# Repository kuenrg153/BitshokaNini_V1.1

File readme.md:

```
Open Source is Intrinsic to Bitcoin
```
# The Bitshoka Nini V1.1
The Bitshoka Nini V1.1 is based off of the Bitaxe Gamma EXCEPT it uses the KF1950 ASIC from MicroBT / Whatsminer.
Huge shoutout to skot for all the work he did create this ecosystem!
The primary aim Bitshoka Nini is to bring microBT ASICs to the Bitaxe ecosystem. A secondary goal is to make a low cost and readily available Bitaxe variant in Africa.
We hope that this is the first of a number of contributions the Bitshoka team can make to the bitcoin network.
Shoka is "axe" and Nini is "what" in Swahili.

# The bitaxe
bitaxe is a fully open source Bitcoin ASIC miner aimed at decentralizing mining. 

## Goals
- **Easy**: Just plug it in and mine Bitcoin over WiFi. No external computer needed.
- **Practical**: low cost, low noise, low power, low maintenance. You can run this at home.
- **ASIC Power**: High efficiency and hashrate, based on the latest and greatest Application Specific Integrated Circuits.
- **Versatile**: Mine to any StratumV1 pool, Lottery mine, Solo mine, Or hack it to do whatever you want.
- **Bitcoin Ethos**: Fully open source, permissionless and decentralized to support the worldwide freedom money.

## ASIC
At the heart of the bitaxeGamma is a BM1370 Bitcoin mining ASIC from the Antminer S21 Pro from Bitmain. It's not open source.

- Bitmain claims the BM1370 has 15 J/TH efficiency. We can get pretty close to that with the BitaxeGamma
- The Antminer S21 Pro has a nominal hashrate of 234 TH/s. There are 3 hashboards with 65 chips each, for a total of 195 chips. The bitaxeGamma has a single one of these chips. That means _about_ 1.2 TH/s per bitaxeGamma. Initial testing looks good!
- The BM1370 is brand new and isn't available individually yet. The best place to get these chips is right out of a S21 Pro.
- The BM1370 has a different footprint and pinout from the BM1368, BM1366, BM1397 and BM1387 in previous bitaxe.

## Current Status
- BitaxeGamma 600 is working well and has been released!
- In addition to higher hashrate, the Gamma also uses more power. Please pay attemtion to hash frequency and voltage settings as it's much easier to overheat, especially when using the stock heatsink and fan.
- BM1370 firmware support has been added to [esp-miner](https://github.com/skot/esp-miner)
- Be sure to check the [HW issues](https://github.com/skot/bitaxe/issues) for known bugs, reworks and errata.
- This is an _advanced_ build! You can do it, but if you're not looking for a project, it might be best to buy one pre-assembled from one of the [many sellers](https://bitaxe.org/legit.html). Check [Skot's method](assembly.md) of hand assembling PCBs.

## PCB Hardware
This repo contains all of the design files for the PCB. [KiCAD](https://www.kicad.com) software is used. There is a BOM file for all of the components that get soldered to the PCB. 

- Order PCBs from your favorite PCB shop, like [JLCPCB](https://jlcpcb.com), [SeeedStudio](https://www.seeedstudio.com/fusion_pcb.html), or [PCBWay](https://www.pcbway.com)
    - Gerbers are in the `Manufacturing Files` dir. PCBs are 4-layer, 6mil trace/space and 0.3mm hole compatible. 1oz outer / 0.5oz inner layer thickness works well.
    - Make sure to order stencils too. These are the "paste" layers in the gerbers folder. one for top and one for bottom.
- All PCB parts except the ASIC are available from [DigiKey](https://www.digikey.com/en/products) and others. You can find Digikey part numbers on the DK tab of the BOM

## Extra Hardware
There are a few other hardware components that are needed for a complete bitaxe.

- **Heatsink**
	- [40x40mm heatsink and 5V fan](https://www.aliexpress.com/item/2251832861666365.html) from a random AliExpress seller. The fans are crap, but the heatsinks are good.  
- **Fan**
	- You **must** have active cooling on the bitaxe. The heatsink alone is not enough.
	- The Bitaxe has a connector for a 4pin, 5V PWM fan. 40mm square, 20mm thick fans work nicely with the suggested heatsink. Make sure to get a 5V fan! 12V spin, but slowly overheating your Bitaxe..
	- Upgrade your fan with the [Noctua NF-A4x10](https://noctua.at/en/nf-a4x10-5v-pwm) 5V 4-Pin fan for a much more pleasant experience.
- **Thermal compound**
	- Use a good quality thermal compound between the heatsink and ASIC. [Thermal Grizzly Kryonaut](https://www.amazon.com/Thermal-Grizzly-Kryonaut-Grease-Paste/dp/B011F7W3LU) has been known to work well.  
- **Display**
	- Supports 0.91" SSD1306-based I2C OLED Module. [Example Amazon seller](https://www.amazon.com/gp/product/B08ZY4YBHL). Make sure to get the male pins to interface with the Bitaxe PCB. 
- **Power Supply**
	- **5V DC Only!** Anything else will damage the Bitaxe. Be careful and double-check your power supply is 5V. Many other voltage power supplies use the same connector.
	- The power supply needs to supply in excess of 4A (20W) and not drop below 5V. Often times you have to use a power supply rated for 25-30W to get this!
 		- The [Meanwell GST60A05-P1J](https://www.digikey.com/en/products/detail/mean-well-usa-inc/GST60A05-P1J/7703709) at 30 Watts is the cadillac of 5V PSUs and is working well with the Gamma.  
	- The bitaxe uses a 5.5x2.1mm, center-positive barrel jack. 5.5x2.5mm plugs have been known to work.
- **Stand**
	- The PCB has corner mounting holes. You're going to want a stand to mount your Bitaxe. Many excellent 3D printed designs are available.

## Firmware
- The [ESP-Miner](https://github.com/skot/ESP-Miner) has initial support for the BM1370 ASIC. Improvements are ongoing.

### ESP32 Programming Requirements
- As of the bitaxeUltra, all ESP32 programming is done through a USB-C cable and connector on the bitaxe. See [ESP-Miner](https://github.com/skot/ESP-Miner) for more details.

## More Information
- Project page at [bitaxe.org](https://bitaxe.org)
- [Open Source Miners United](discord.gg/osmu) Discord chat
- [building.md](building.md) for PCB ordering tips
- [assembly.md](assembly.md) for assembly tips

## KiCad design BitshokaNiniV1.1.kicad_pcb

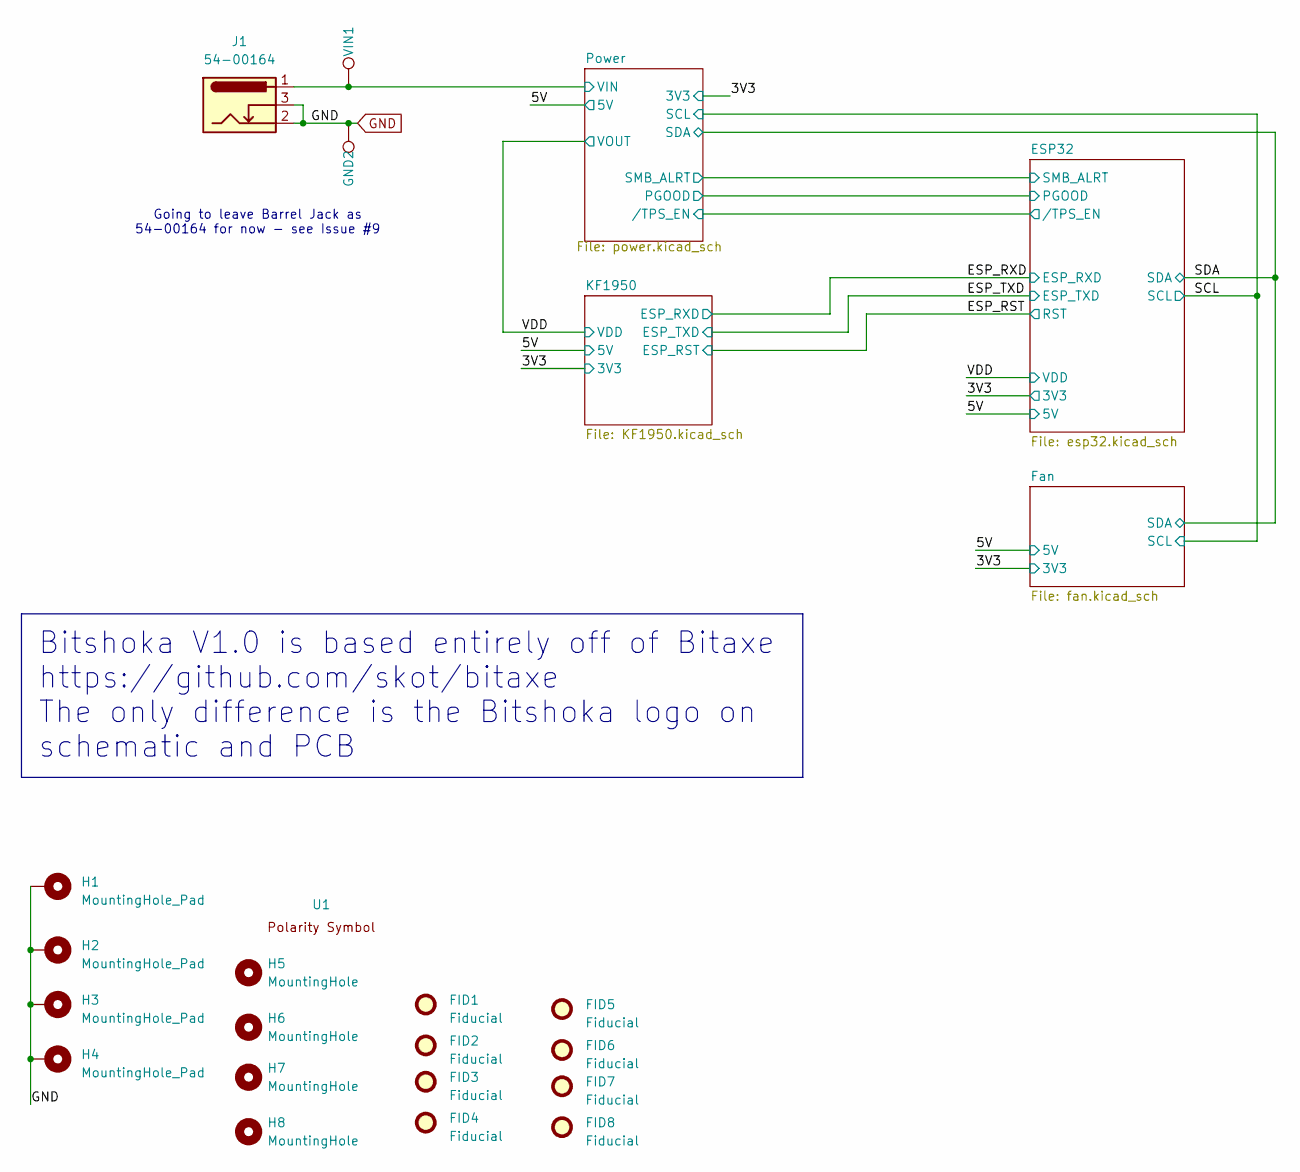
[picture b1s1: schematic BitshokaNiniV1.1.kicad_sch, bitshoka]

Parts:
FID1, FID2, FID3, FID4, FID5, FID6, FID7, FID8: Fiducial; Fiducial_1mm_Mask2mm
GND2: TestPoint; TestPoint_Pad_D1.5mm
H1, H2, H3, H4: MountingHole_Pad; MountingHole_3mm_Pad_Via
H5, H6, H7, H8: MountingHole; MountingHole_3.5mm
J1: 54-00164; TENSILITY_54-00164; PARTNO 54-00164; LCSC C431534
U1: polarity
VIN1: TestPoint; TestPoint_Pad_D1.5mm

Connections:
/5V: J1.1, VIN1.1; also elsewhere on the board
GND: GND2.1, H1.1, H2.1, H3.1, H4.1, J1.2, J1.3; also elsewhere on the board

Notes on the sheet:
Going to leave Barrel Jack as 54-00164 for now - see Issue #9
Bitshoka V1.0 is based entirely off of Bitaxe https://github.com/skot/bitaxe The only difference is the Bitshoka logo on schematic and PCB

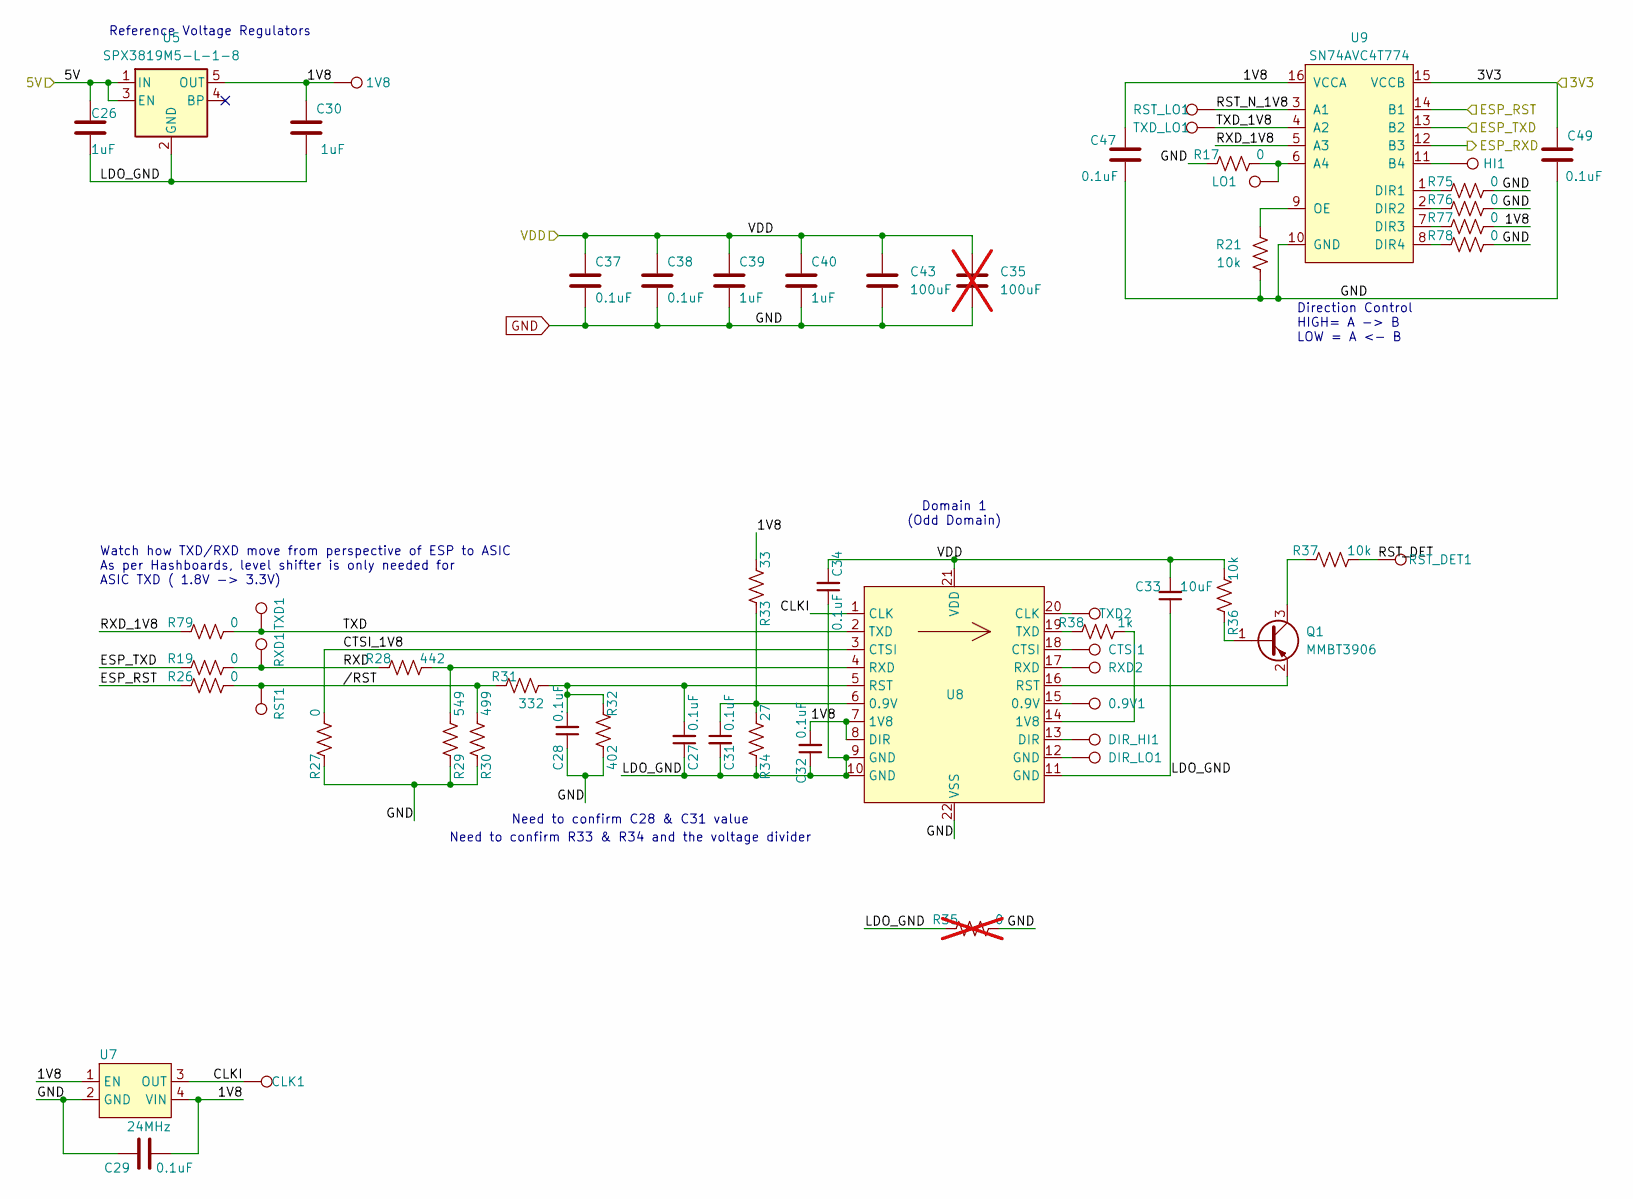
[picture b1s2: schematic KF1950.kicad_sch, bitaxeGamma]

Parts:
0.9V1: TestPoint; TestPoint_Pad_D1.0mm
1V8: TestPoint; TestPoint_Pad_D1.5mm
C26, C30, C39, C40: 1uF; C_0402_1005Metric; PARTNO EMK105BJ105MV-F
C27, C28, C31, C32, C34: 0.1uF; C_0402_1005Metric
C29, C37, C38, C47, C49: 0.1uF; C_0402_1005Metric; PARTNO CL05A104KO5NNNC
C33: 10uF; C_0805_2012Metric
C35: 100uF; C_1206_3216Metric; not fitted
C43: 100uF; C_1206_3216Metric
CLK1: TestPoint; TestPoint_Pad_D1.5mm
CTSI1: TestPoint; TestPoint_Pad_D1.0mm
DIR_HI1: TestPoint; TestPoint_Pad_D1.0mm
DIR_LO1: TestPoint; TestPoint_Pad_D1.0mm
HI1: TestPoint; TestPoint_Pad_D1.5mm
LO1: TestPoint; TestPoint_Pad_D1.5mm
Q1: MMBT3906; SOT-23
R17, R19, R26, R27, R79: 0; R_0402_1005Metric
R21: 10k; R_0402_1005Metric; PARTNO RC0402FR-0720KL
R28: 442; R_0402_1005Metric
R29: 549; R_0402_1005Metric
R30: 499; R_0402_1005Metric
R31: 332; R_0402_1005Metric
R32: 402; R_0402_1005Metric
R33: 33; R_0402_1005Metric
R34: 27; R_0402_1005Metric
R35: 0; R_0402_1005Metric; not fitted
R36, R37: 10k; R_0402_1005Metric
R38: 1k; R_0402_1005Metric
R75, R76, R77, R78: 0; R_0402_1005Metric; PARTNO RC0402FR-0720KL
RST1: TestPoint; TestPoint_Pad_D1.5mm
RST_DET1: TestPoint; TestPoint_Pad_D1.5mm
RST_LO1: TestPoint; TestPoint_Pad_D1.5mm
RXD1: TestPoint; TestPoint_Pad_D1.5mm
RXD2: TestPoint; TestPoint_Pad_D1.0mm
TXD1: TestPoint; TestPoint_Pad_D1.5mm
TXD2: TestPoint; TestPoint_Pad_D1.0mm
TXD_LO1: TestPoint; TestPoint_Pad_D1.5mm
U5: SPX3819M5-L-1-8; SOT-23-5
U7: 24MHz; SMD3225-4P; PARTNO SX3M25.000E20F30THN; LCSC C5137262
U8: KF1950
U9: SN74AVC4T774; TSSOP-16_4.4x5mm_P0.65mm; PARTNO SN74AVC4T774PWR

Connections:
/3V3: C49.1, U9.15 (VCCB); also elsewhere on the board
/5V: C26.1, U5.1 (IN), U5.3 (EN); also elsewhere on the board
/ESP_RST: R26.1, U9.14 (B1); also elsewhere on the board
/ESP_RXD: U9.12 (B3); also elsewhere on the board
/ESP_TXD: R19.1, U9.13 (B2); also elsewhere on the board
/KF1950/1V8: 1V8.1, C29.2, C30.1, C32.2, C47.1, R33.2, R77.1, U5.5 (OUT), U7.1 (EN), U7.4 (VIN), U8.7 (1V8), U8.8 (DIR), U9.16 (VCCA)
/KF1950/CLKI: CLK1.1, U7.3 (OUT), U8.1 (CLK)
/KF1950/CTSI_1V8: R27.2, U8.3 (CTSI)
/KF1950/LDO_GND: C26.2, C27.1, C30.2, C31.2, C32.1, C33.1, C34.1, R34.1, R35.1, U5.2 (GND), U8.9 (GND), U8.10 (GND), U8.11 (GND)
/KF1950/RST_DET: R37.2, RST_DET1.1
/KF1950/RST_N_1V8: RST_LO1.1, U9.3 (A1)
/KF1950/RXD: R19.2, R28.1, RXD1.1
/KF1950/RXD_1V8: R79.1, U9.5 (A3)
/KF1950/TXD: R79.2, TXD1.1, U8.2 (TXD)
/KF1950/TXD_1V8: TXD_LO1.1, U9.4 (A2)
/KF1950//RST: R26.2, R30.2, R31.1, RST1.1
/VDD: C33.2, C34.2, C35.1, C37.1, C38.1, C39.1, C40.1, C43.1, R36.1, U8.21 (VDD); also elsewhere on the board
GND: C28.1, C29.1, C35.2, C37.2, C38.2, C39.2, C40.2, C43.2, C47.2, C49.2, R17.1, R21.1, R27.1, R29.1, R30.1, R32.2, R35.2, R75.1, R76.1, R78.1, U7.2 (GND), U8.22 (VSS), U9.10 (GND); also elsewhere on the board
unnamed: 0.9V1.1, U8.15 (0.9V)
unnamed: C27.2, C28.2, R31.2, R32.1, U8.5 (RST)
unnamed: C31.1, R33.1, R34.2, U8.6 (0.9V)
unnamed: CTSI1.1, U8.18 (CTSI)
unnamed: DIR_HI1.1, U8.13 (DIR)
unnamed: DIR_LO1.1, U8.12 (GND)
unnamed: Q1.1 (B), R36.2
unnamed: Q1.3 (C), R37.1
unnamed: Q1.2 (E), U8.16 (RST)
unnamed: R28.2, R29.2, U8.4 (RXD)
unnamed: R38.1, U8.14 (1V8)
unnamed: R38.2, U8.19 (TXD)
unnamed: RXD2.1, U8.17 (RXD)
unnamed: TXD2.1, U8.20 (CLK)
unnamed: LO1.1, R17.2, U9.6 (A4)
unnamed: HI1.1, U9.11 (B4)
unnamed: R75.2, U9.1 (DIR1)
unnamed: R76.2, U9.2 (DIR2)
unnamed: R77.2, U9.7 (DIR3)
unnamed: R78.2, U9.8 (DIR4)
unnamed: R21.2, U9.9 (OE)

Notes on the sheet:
Reference Voltage Regulators
Need to confirm C28 & C31 value
Domain 1 (Odd Domain)
Direction Control HIGH= A -> B LOW = A <- B
Watch how TXD/RXD move from perspective of ESP to ASIC As per Hashboards, level shifter is only needed for ASIC TXD ( 1.8V -> 3.3V)
Need to confirm R33 & R34 and the voltage divider

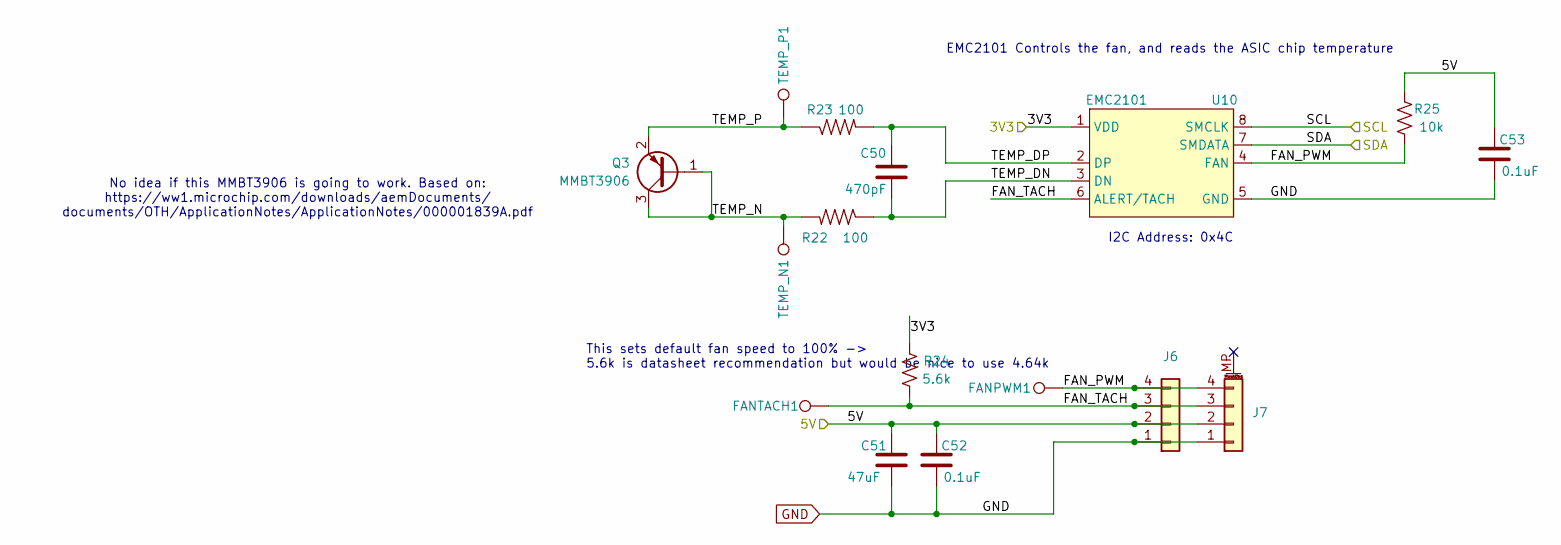
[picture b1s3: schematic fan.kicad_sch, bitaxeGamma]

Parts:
C50: 470pF; C_0402_1005Metric; PARTNO CL05B471KB5NNNC
C51: 47uF; C_1210_3225Metric; PARTNO CL32A476KOJNNNE
C52, C53: 0.1uF; C_0402_1005Metric; PARTNO CL05A104KO5NNNC
FANPWM1: TestPoint; TestPoint_Pad_D1.5mm
FANTACH1: TestPoint; TestPoint_Pad_D1.5mm
J6: Conn_01x04; 470531000; PARTNO 0470531000
J7: Conn_01x04; JST_SH_BM04B-SRSS-TB_1x04-1MP_P1.00mm_Vertical
Q3: MMBT3906; SOT-23
R22, R23: 100; R_0402_1005Metric; PARTNO RC0402FR-07100RL
R24: 5.6k; R_0402_1005Metric; PARTNO RC0402FR-135K6L
R25: 10k; R_0402_1005Metric; PARTNO RC0402JR-0710KL
TEMP_N1: TestPoint; TestPoint_Pad_D1.5mm
TEMP_P1: TestPoint; TestPoint_Pad_D1.5mm
U10: EMC2101; TSSOP-8_3x3mm_P0.65mm; PARTNO EMC2101-R-ACZL-TR

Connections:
/3V3: R24.2, U10.1 (VDD); also elsewhere on the board
/5V: C51.1, C52.1, C53.1, J6.2, J7.2, R25.2; also elsewhere on the board
/Fan/FAN_PWM: FANPWM1.1, J6.4, J7.4, R25.1, U10.4 (FAN)
/Fan/FAN_TACH: FANTACH1.1, J6.3, J7.3, R24.1, U10.6 (ALERT/TACH)
/Fan/TEMP_DN: C50.2, R22.1, U10.3 (DN)
/Fan/TEMP_DP: C50.1, R23.2, U10.2 (DP)
/Fan/TEMP_N: Q3.1 (B), Q3.3 (C), R22.2, TEMP_N1.1
/Fan/TEMP_P: Q3.2 (E), R23.1, TEMP_P1.1
/SCL: U10.8 (SMCLK); also elsewhere on the board
/SDA: U10.7 (SMDATA); also elsewhere on the board
GND: C51.2, C52.2, C53.2, J6.1, J7.1, U10.5 (GND); also elsewhere on the board

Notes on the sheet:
EMC2101 Controls the fan, and reads the ASIC chip temperature
This sets default fan speed to 100% -> 5.6k is datasheet recommendation but would be nice to use 4.64k
No idea if this MMBT3906 is going to work. Based on: https://ww1.microchip.com/downloads/aemDocuments/ documents/OTH/ApplicationNotes/ApplicationNotes/000001839A.pdf
I2C Address: 0x4C

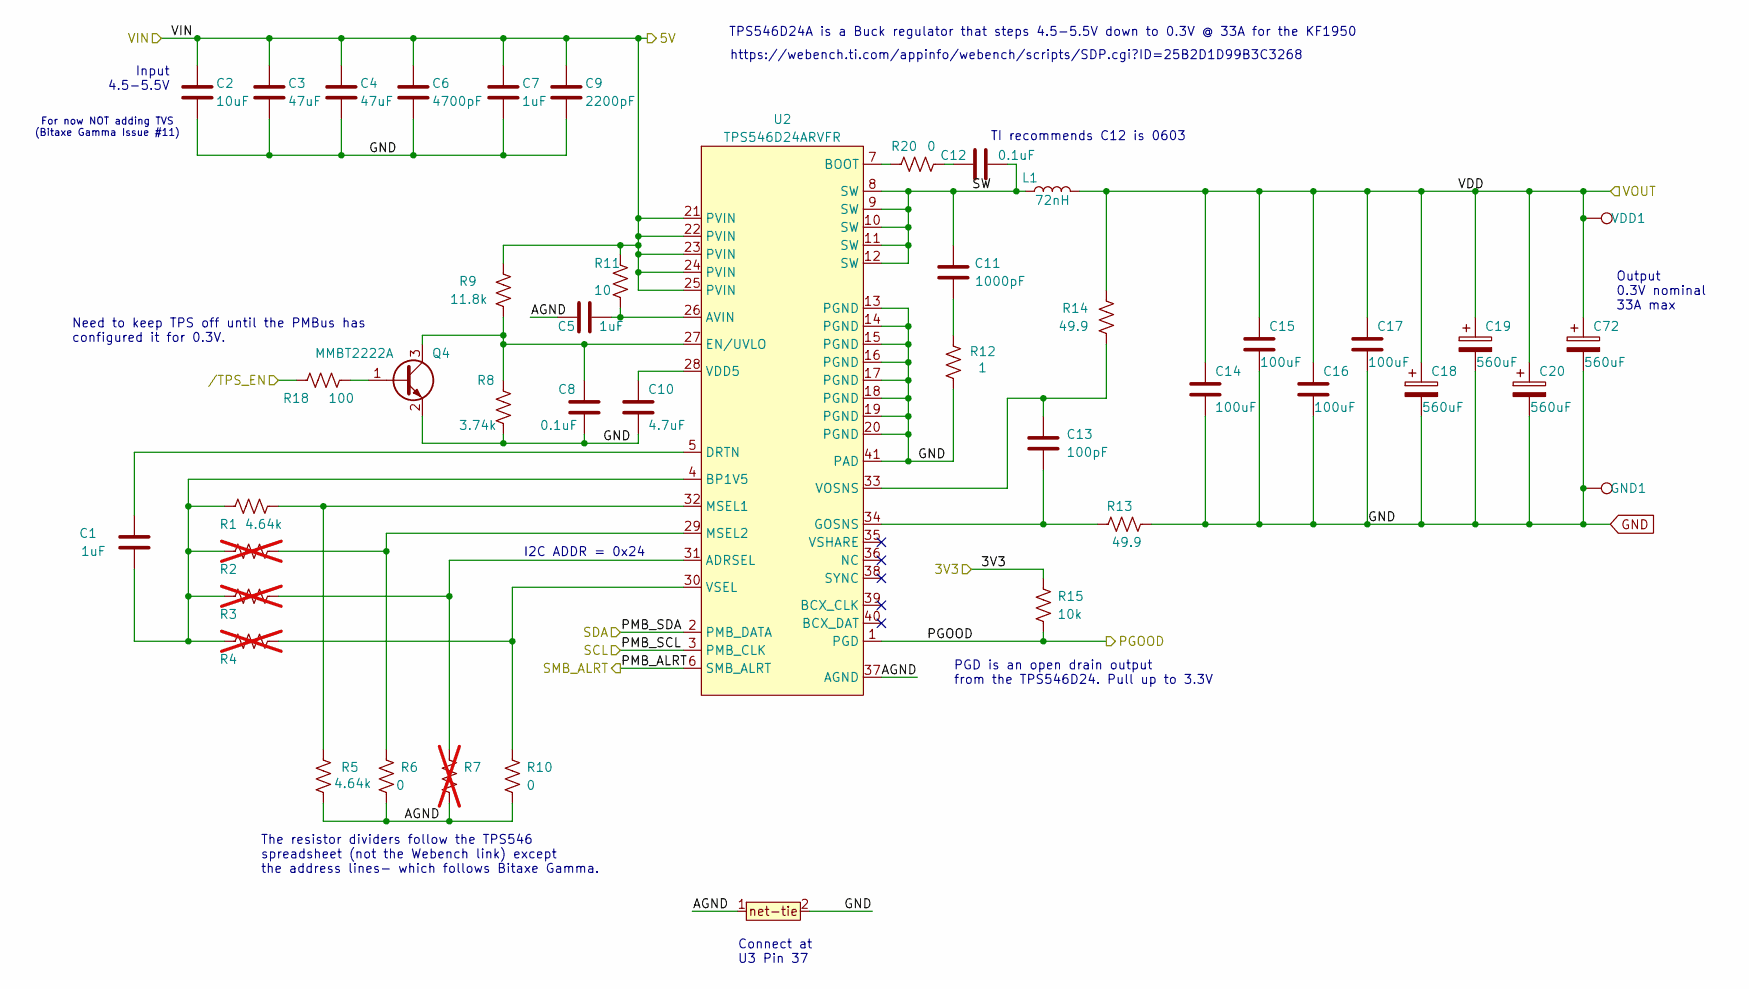
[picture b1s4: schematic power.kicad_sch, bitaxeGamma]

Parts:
C1, C5, C7: 1uF; C_0402_1005Metric; PARTNO EMK105BJ105MV-F
C2: 10uF; C_0805_2012Metric; PARTNO CL21A106KOQNNNE
C3, C4: 47uF; C_1210_3225Metric; PARTNO CL32A476KOJNNNE
C6: 4700pF; C_0402_1005Metric; PARTNO GRM155R71E472KA01D
C8: 0.1uF; C_0402_1005Metric; PARTNO CL05A104KO5NNNC
C9: 2200pF; C_0402_1005Metric; PARTNO GRM155R61H222KA01D
C10: 4.7uF; C_0402_1005Metric; PARTNO GRM155R61A475MEAAD
C11: 1000pF; C_0402_1005Metric; PARTNO CC0805KRX7R9BB102
C12: 0.1uF; C_0603_1608Metric; PARTNO CL05A104KO5NNNC
C13: 100pF; C_0402_1005Metric; PARTNO 885012005013
C14: 100uF; C_1206_3216Metric; PARTNO GRM32EC80J107ME20L
C15, C16, C17: 100uF; C_1206_3216Metric
C18, C19, C20, C72: 560uF; EEF-GX; PARTNO EEF-GX0D561R
GND1: TestPoint; TestPoint_Pad_D1.5mm
L1: 72nH; FP0805R1; PARTNO FP0805R1-R07-R
Q4: MMBT2222A; SOT-23
R1: 4.64k; R_0402_1005Metric; PARTNO RC0402FR-078K25L
R2, R3, R4, R7: R_0402_1005Metric; not fitted
R5: 4.64k; R_0402_1005Metric; PARTNO RC0402FR-0714K7L
R6: 0; R_0402_1005Metric; PARTNO RC0402JR-070RL
R8: 3.74k; R_0402_1005Metric; PARTNO RC0402FR-073K74L
R9: 11.8k; R_0402_1005Metric; PARTNO RC0402FR-0711K8L
R10: 0; R_0402_1005Metric; PARTNO RC0402FR-0768K1L
R11: 10; R_0402_1005Metric; PARTNO RC0402FR-0710RL
R12: 1; R_1206_3216Metric; PARTNO CSR1206FT1R00
R13, R14: 49.9; R_0402_1005Metric; PARTNO RC0402FR-0749R9L
R15: 10k; R_0402_1005Metric; PARTNO RC0402JR-0710KL
R18: 100; R_0402_1005Metric; PARTNO RC0402FR-078K25L
R20: 0; R_0402_1005Metric; PARTNO CSR1206FT1R00
T1: net-tie; NetTie-0.25mm
U2: TPS546D24ARVFR; LQFN40-CLIP; PARTNO TPS546D24ARVFR
VDD1: TestPoint; TestPoint_Pad_D1.5mm

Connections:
/3V3: R15.2; also elsewhere on the board
/5V: C2.1, C3.1, C4.1, C6.1, C7.1, C9.1, R9.1, R11.1, U2.21 (PVIN), U2.22 (PVIN), U2.23 (PVIN), U2.24 (PVIN), U2.25 (PVIN); also elsewhere on the board
/ESP32//TPS_EN: R18.1; also elsewhere on the board
/Power/AGND: C5.2, R5.1, R6.2, R7.2, R10.2, T1.1, U2.37 (AGND)
/Power/PGOOD: R15.1, U2.1 (PGD); also elsewhere on the board
/Power/PMB_ALRT: U2.6 (SMB_ALRT); also elsewhere on the board
/Power/SW: C11.2, C12.2, L1.1, U2.8 (SW), U2.9 (SW), U2.10 (SW), U2.11 (SW), U2.12 (SW)
/SCL: U2.3 (PMB_CLK); also elsewhere on the board
/SDA: U2.2 (PMB_DATA); also elsewhere on the board
/VDD: C14.1, C15.1, C16.1, C17.1, C18.1, C19.1, C20.1, C72.1, L1.2, R14.1, VDD1.1; also elsewhere on the board
GND: C2.2, C3.2, C4.2, C6.2, C7.2, C8.2, C9.2, C10.2, C14.2, C15.2, C16.2, C17.2, C18.2, C19.2, C20.2, C72.2, GND1.1, Q4.2 (E), R8.2, R12.1, R13.2, T1.2, U2.13 (PGND), U2.14 (PGND), U2.15 (PGND), U2.16 (PGND), U2.17 (PGND), U2.18 (PGND), U2.19 (PGND), U2.20 (PGND), U2.41 (PAD); also elsewhere on the board
unnamed: C11.1, R12.2
unnamed: C12.1, R20.1
unnamed: Q4.1 (B), R18.2
unnamed: C8.1, Q4.3 (C), R8.1, R9.2, U2.27 (EN/UVLO)
unnamed: R3.2, R7.1, U2.31 (ADRSEL)
unnamed: C5.1, R11.2, U2.26 (AVIN)
unnamed: R20.2, U2.7 (BOOT)
unnamed: C1.2, R1.1, R2.1, R3.1, R4.1, U2.4 (BP1V5)
unnamed: C1.1, U2.5 (DRTN)
unnamed: C13.2, R13.1, U2.34 (GOSNS)
unnamed: R1.2, R5.2, U2.32 (MSEL1)
unnamed: R2.2, R6.1, U2.29 (MSEL2)
unnamed: C10.1, U2.28 (VDD5)
unnamed: C13.1, R14.2, U2.33 (VOSNS)
unnamed: R4.2, R10.1, U2.30 (VSEL)

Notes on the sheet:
Input 4.5-5.5V
https://webench.ti.com/appinfo/webench/scripts/SDP.cgi?ID=25B2D1D99B3C3268
Need to keep TPS off until the PMBus has configured it for 0.3V.
The resistor dividers follow the TPS546 spreadsheet (not the Webench link) except the address lines- which follows Bitaxe Gamma.
PGD is an open drain output from the TPS546D24. Pull up to 3.3V
For now NOT adding TVS (Bitaxe Gamma Issue #11)
I2C ADDR = 0x24
TPS546D24A is a Buck regulator that steps 4.5-5.5V down to 0.3V @ 33A for the KF1950
TI recommends C12 is 0603
Output 0.3V nominal 33A max
Connect at U3 Pin 37

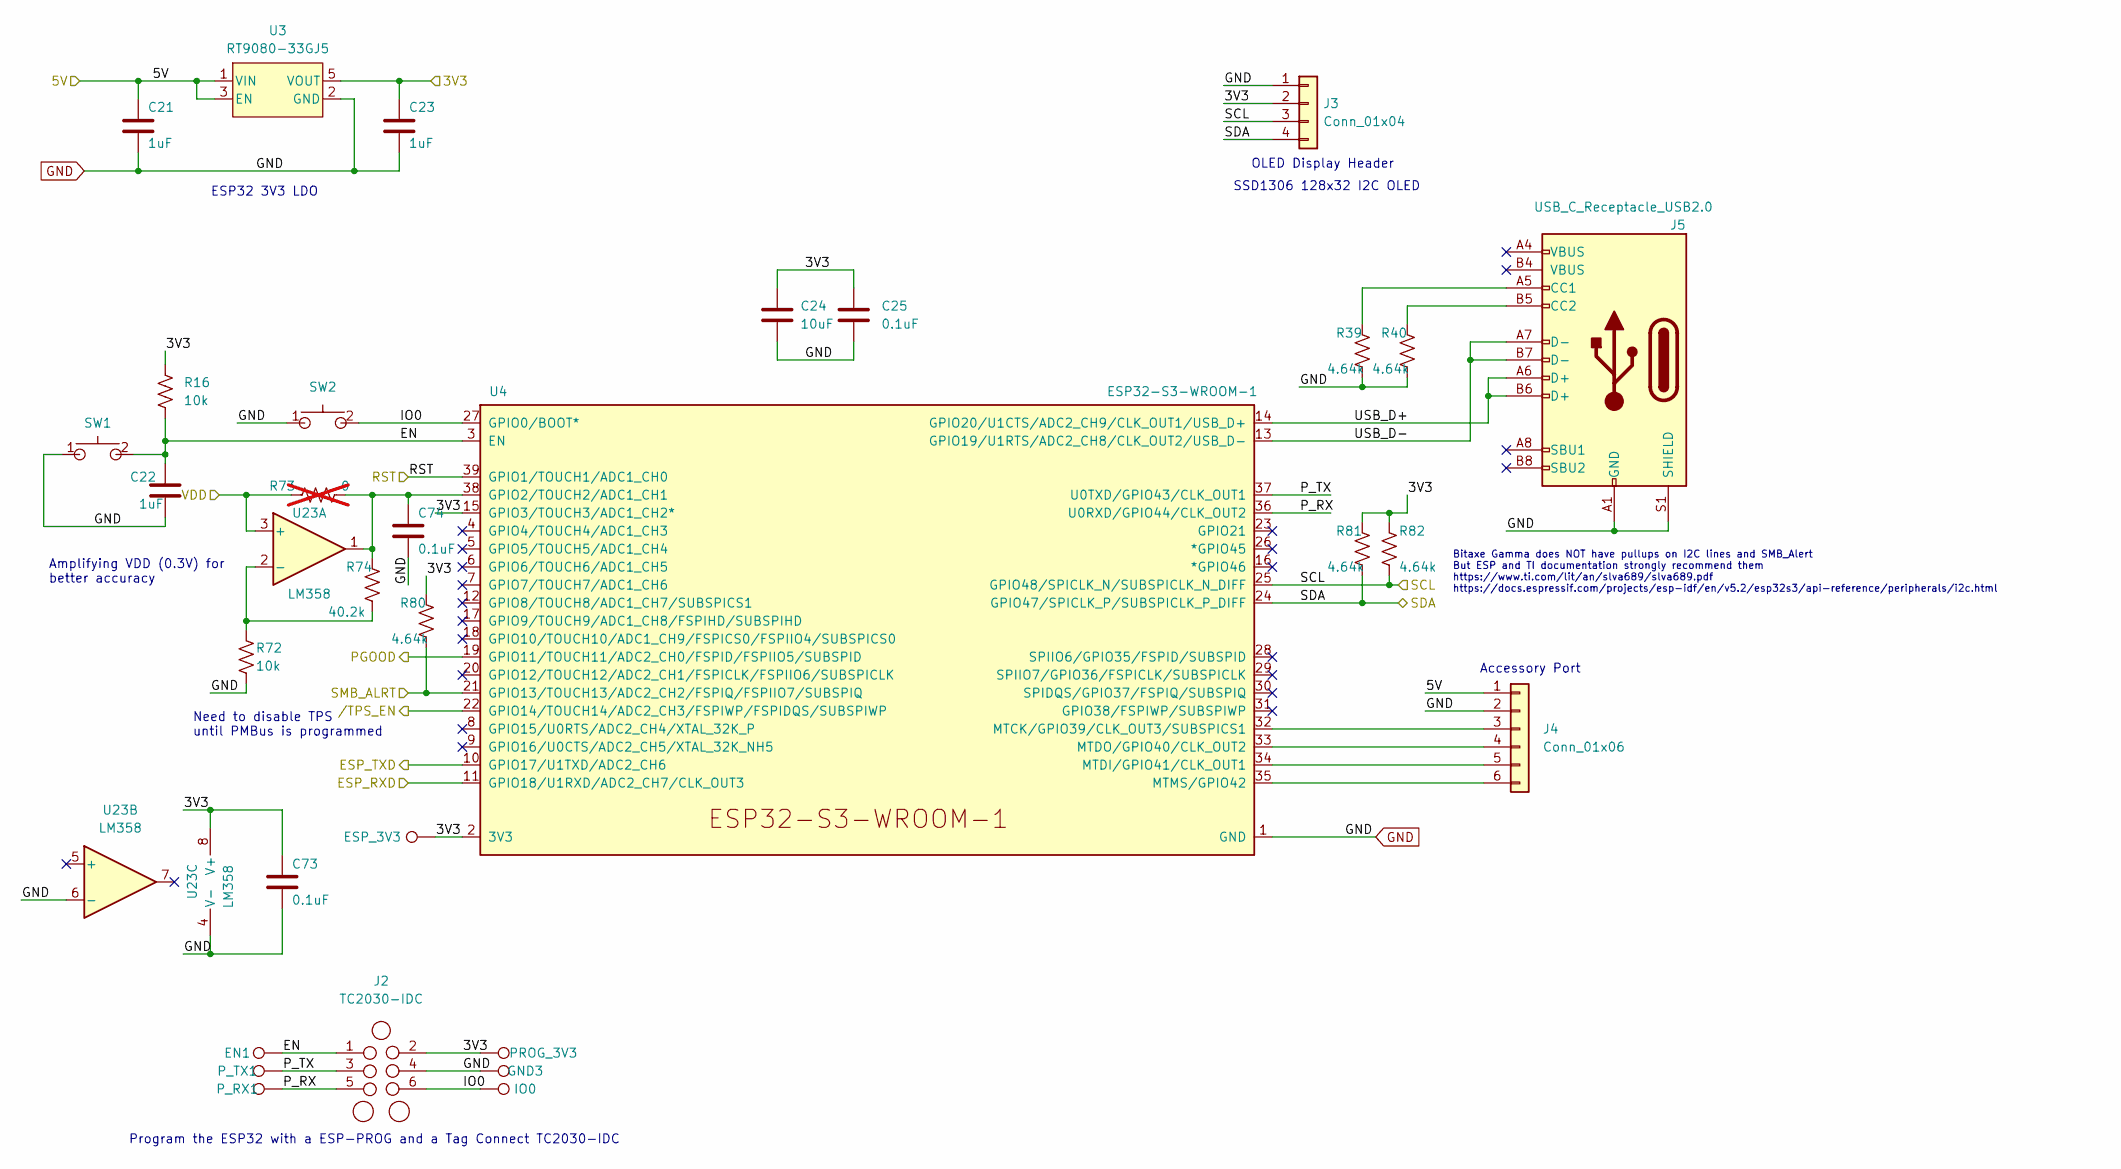
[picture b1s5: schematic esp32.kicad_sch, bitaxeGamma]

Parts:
C21, C22, C23: 1uF; C_0402_1005Metric; PARTNO EMK105BJ105MV-F
C24: 10uF; C_0805_2012Metric; PARTNO CL21A106KOQNNNE
C25: 0.1uF; C_0402_1005Metric; PARTNO CL05A104KO5NNNC
C73, C74: 0.1uF; C_0402_1005Metric; PARTNO EMK105BJ105MV-F
EN1: TestPoint; TestPoint_Pad_D1.5mm
ESP_3V3: TestPoint; TestPoint_Pad_D1.5mm
GND3: TestPoint; TestPoint_Pad_D1.5mm
IO0: TestPoint; TestPoint_Pad_D1.5mm
J2: TC2030-IDC; Tag-Connect_TC2030-IDC-NL_2x03_P1.27mm_Vertical
J3: Conn_01x04; PinHeader_1x04_P2.54mm_Vertical_shifted
J4: Conn_01x06; PinHeader_1x06_P2.54mm_Vertical
J5: USB_C_Receptacle_USB2.0; USB_C_Receptacle_GCT_USB4105-xx-A; PARTNO USB4105-GF-A
PROG_3V3: TestPoint; TestPoint_Pad_D1.5mm
P_RX1: TestPoint; TestPoint_Pad_D1.5mm
P_TX1: TestPoint; TestPoint_Pad_D1.5mm
R16, R72: 10k; R_0402_1005Metric; PARTNO RC0402JR-0710KL
R39, R40, R80, R81, R82: 4.64k; R_0402_1005Metric; PARTNO RC0402JR-0710KL
R73: 0; R_0402_1005Metric; PARTNO RC0402JR-0710KL; not fitted
R74: 40.2k; R_0402_1005Metric; PARTNO RC0402JR-0710KL
SW1, SW2: GT-TC029B-H025-L1N; SW_CS1213AGF260_CRS; PARTNO CS1213AGF260
U3: RT9080-33GJ5; PARTNO RT9080-33GJ5
U4: ESP32-S3-WROOM-1; PARTNO ESP32-S3-WROOM-1-N16R8
U23: LM358; TSSOP-8_4.4x3mm_P0.65mm

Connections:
/3V3: C23.1, C24.1, C25.1, C73.1, ESP_3V3.1, J2.2, J3.2, PROG_3V3.1, R16.1, R80.1, R81.1, R82.1, U3.5 (VOUT), U4.2 (3V3), U4.15 (GPIO3/TOUCH3/ADC1_CH2*), U23.8 (V+); also elsewhere on the board
/5V: C21.1, J4.1, U3.1 (VIN), U3.3 (EN); also elsewhere on the board
/ESP32/EN: C22.1, EN1.1, J2.1, R16.2, SW1.2, U4.3 (EN)
/ESP32/IO0: IO0.1, J2.6, SW2.2, U4.27 (GPIO0/BOOT*)
/ESP32/P_RX: J2.5, P_RX1.1, U4.36 (U0RXD/GPIO44/CLK_OUT2)
/ESP32/P_TX: J2.3, P_TX1.1, U4.37 (U0TXD/GPIO43/CLK_OUT1)
/ESP32/USB_D+: J5.A6 (D+), J5.B6 (D+), U4.14 (GPIO20/U1CTS/ADC2_CH9/CLK_OUT1/USB_D+)
/ESP32/USB_D-: J5.A7 (D-), J5.B7 (D-), U4.13 (GPIO19/U1RTS/ADC2_CH8/CLK_OUT2/USB_D-)
/ESP32//TPS_EN: U4.22 (GPIO14/TOUCH14/ADC2_CH3/FSPIWP/FSPIDQS/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); also elsewhere on the board
/ESP_RST: U4.39 (GPIO1/TOUCH1/ADC1_CH0); also elsewhere on the board
/ESP_RXD: U4.11 (GPIO18/U1RXD/ADC2_CH7/CLK_OUT3); also elsewhere on the board
/ESP_TXD: U4.10 (GPIO17/U1TXD/ADC2_CH6); also elsewhere on the board
/Power/PGOOD: U4.19 (GPIO11/TOUCH11/ADC2_CH0/FSPID/FSPIIO5/S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); also elsewhere on the board
/Power/PMB_ALRT: R80.2, U4.21 (GPIO13/TOUCH13/ADC2_CH2/FSPIQ/FSPIIO7/S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); also elsewhere on the board
/SCL: J3.3, R82.2, U4.25 (GPIO48/SPICLK_N/SUBSPICLK_N_DIFF); also elsewhere on the board
/SDA: J3.4, R81.2, U4.24 (GPIO47/SPICLK_P/SUBSPICLK_P_DIFF); also elsewhere on the board
/VDD: R73.1, U23.3 (+); also elsewhere on the board
GND: C21.2, C22.2, C23.2, C24.2, C25.2, C73.2, C74.2, GND3.1, J2.4, J3.1, J4.2, J5.A1 (GND), J5.B1 (GND), J5.S1 (SHIELD), R39.2, R40.2, R72.1, SW1.1, SW2.1, U3.2 (GND), U4.1 (GND), U4.40 (GND), U4.41 (GND), U23.4 (V-), U23.6 (-); also elsewhere on the board
unnamed: J4.3, U4.32 (MTCK/GPIO39/CLK_OUT3/SUBSPICS1)
unnamed: J4.4, U4.33 (MTDO/GPIO40/CLK_OUT2)
unnamed: J4.5, U4.34 (MTDI/GPIO41/CLK_OUT1)
unnamed: J4.6, U4.35 (MTMS/GPIO42)
unnamed: J5.A5 (CC1), R39.1
unnamed: J5.B5 (CC2), R40.1
unnamed: C74.1, R73.2, R74.1, U4.38 (GPIO2/TOUCH2/ADC1_CH1), U23.1
unnamed: R72.2, R74.2, U23.2 (-)

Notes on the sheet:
Accessory Port
ESP32 3V3 LDO
Program the ESP32 with a ESP-PROG and a Tag Connect TC2030-IDC
Bitaxe Gamma does NOT have pullups on I2C lines and SMB_Alert But ESP and TI documentation strongly recommend them https://www.ti.com/lit/an/slva689/slva689.pdf https://docs.espressif.com/projects/esp-idf/en/v5.2/esp32s3/api-reference/peripherals/i2c.html
Amplifying VDD (0.3V) for better accuracy
SSD1306 128x32 I2C OLED
Need to disable TPS until PMBus is programmed
OLED Display Header

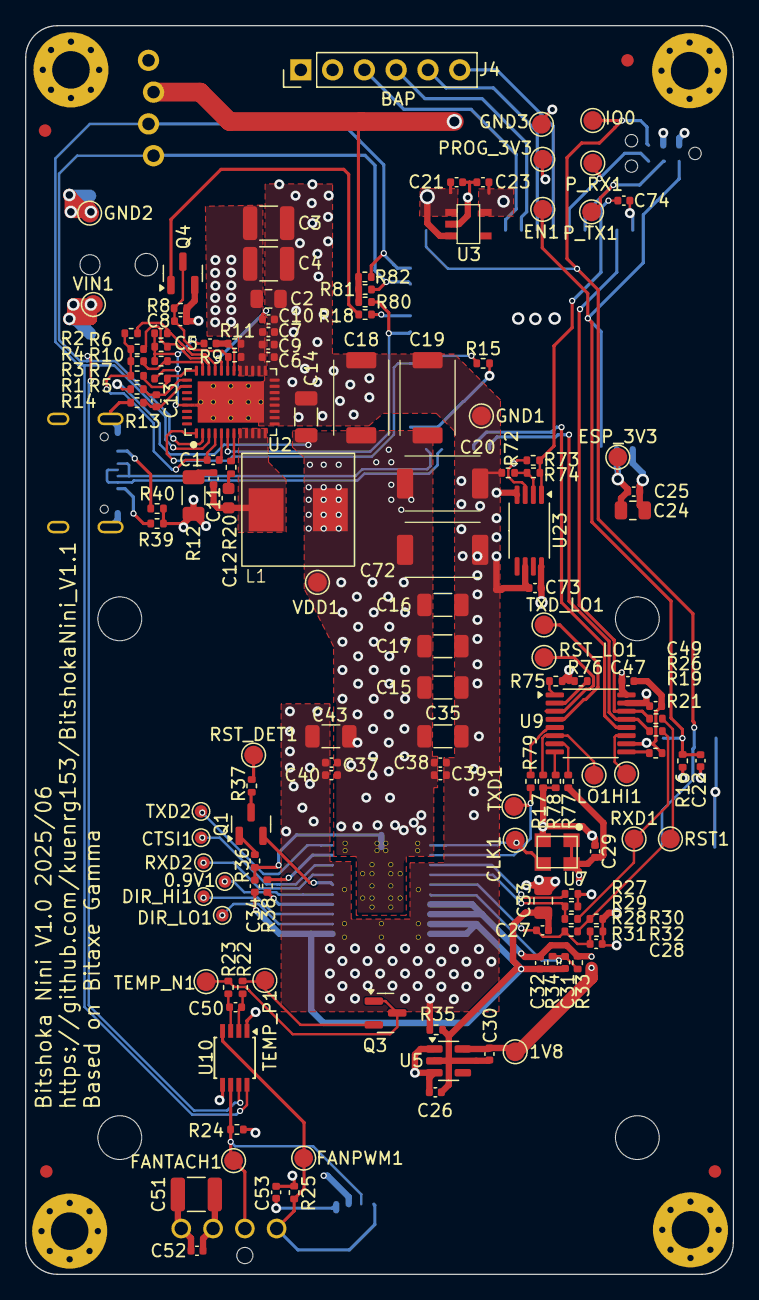
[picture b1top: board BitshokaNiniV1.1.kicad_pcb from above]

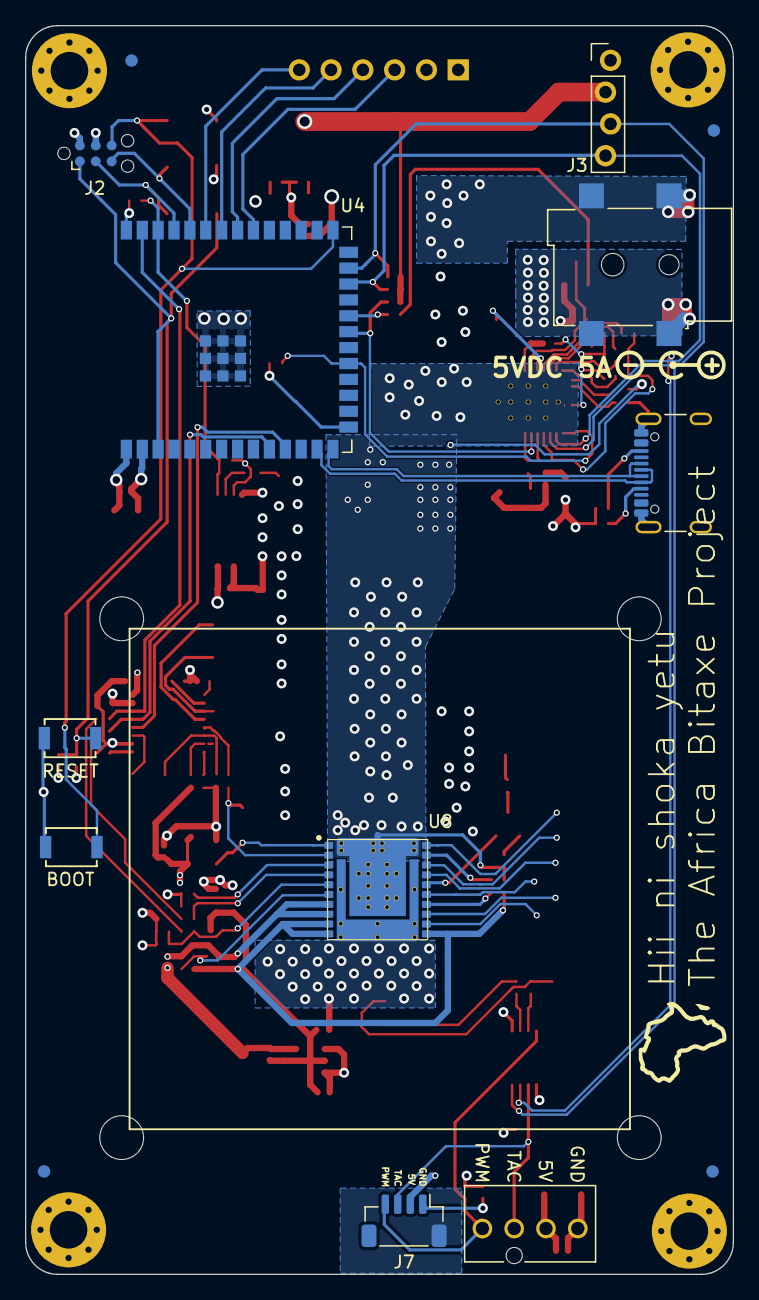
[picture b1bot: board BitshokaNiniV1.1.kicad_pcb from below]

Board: 4 copper layers, 56.5 x 99.8 mm, 171 parts (15 on the bottom side), 81 nets.

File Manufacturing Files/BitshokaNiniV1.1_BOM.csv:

Comment,Reference,,PARTNO,DK,LCSC,DNP,,,,
4700pF,C6,,GRM155R71E472KA01D,490-1309-1-ND,,,,,,
2200pF,C9,,GRM155R61H222KA01D,490-8257-1-ND,,,,,,
4.7uF,C10,,GRM155R61A475MEAAD,490-14306-1-ND,,,,,,
1000pF,C11,,CC0805KRX7R9BB102,311-1127-1-ND,,,,,,
0.1uF,C12,,CL05A104KO5NNNC,1276-1234-1-ND,,,,,,
100pF,C13,,8.85E+11,732-7431-1-ND,,,,,,
100uF,C35,,,,,DNP,,,,
470pF,C50,,CL05B471KB5NNNC,1276-1566-1-ND,,,,,,
1uF,C1 C5 C7 C21 C22 C23 C26 C30 C39 C40,,EMK105BJ105MV-F,587-5514-1-ND,,,,,,
100uF,C14 C15 C16 C17 C43,,GRM32EC80J107ME20L,,,,,,,
560uF,C18 C19 C20 C72,,EEF-GX0D561R,,,,,,,
10uF,C2 C24 C33,,CL21A106KOQNNNE,1276-1096-1-ND,,,,,,
47uF,C3 C4 C51,,CL32A476KOJNNNE,1276-3376-1-ND,,,,,,
0.1uF,C8 C25 C27 C28 C29 C31 C32 C34 C37 C38 C47 C49 C52 C53 C73 C74,,CL05A104KO5NNNC,EMK105BJ105MV-F,1276-1234-1-ND,587-5514-1-ND,,,,
54-00164,J1,,54-00164,839-54-00164CT-ND,C431534,,,,,
USB_C_Receptacle_USB2.0,J5,,USB4105-GF-A,2073-USB4105-GF-ACT-ND,,,,,,
Conn_01x04,J6,,470531000,WM4330-ND,,,,,,
Conn_01x04,J7,,,,,DNP,,,,
72nH,L1,,FP0805R1-R07-R,,,,,,,
MMBT2222A,Q4,,MMBT2222A,,,,,,,
MMBT3906,Q1 Q3,,MMBT3906,,,,,,,
3.74k,R8,,RC0402FR-073K74L,311-3.74KLRCT-ND,,,,,,
11.8k,R9,,RC0402FR-0711K8L,YAG2958CT-ND,,,,,,
10,R11,,RC0402FR-0710RL,311-10.0LRCT-ND,,,,,,
1,R12,,CSR1206FT1R00,CSR1206FT1R00CT-ND,,,,,,
5.6k,R24,,RC0402FR-135K6L,13-RC0402FR-135K6LCT-ND,,,,,,
442,R28,,RT0402BRD07442RL,,,,,,,
549,R29,,RC0402FR-07549RL,,,,,,,
499,R30,,RC0402FR-07499RL,,,,,,,
332,R31,,RC0402FR-07332RL,,,,,,,
402,R32,,RC0402FR-07402RL,,,,,,,
33,R33,,RC0402FR-1333RL,,,,,,,
27,R34,,RC0402JR-0727RL,,,,,,,
1k,R38,,RC0402FR-071KL,,,,,,,
40.2k,R74,,RC0402JR-0710KL,311-10KJRCT-ND,,,,,,
4.64k,R1 R5 R39 R40 R80 R81 R82,,RC0402FR-0714K7L,RC0402FR-078K25L,RC0402JR-0710KL,311-10KJRCT-ND,311-8.25KLRCT-ND,YAG2984CT-ND,,
49.9,R13 R14,,RC0402FR-0749R9L,311-49.9LRCT-ND,,,,,,
10k,R15 R16 R21 R25 R36 R37 R72,,RC0402FR-0720KL,RC0402JR-0710KL,311-10KJRCT-ND,311-20.0KLRCT-ND,,,,
100,R18 R22 R23,,RC0402FR-07100RL,RC0402FR-078K25L,311-100LRCT-ND,311-8.25KLRCT-ND,,,,
0,R35 R73,,RC0402JR-0710KL,311-10KJRCT-ND,,DNP,,,,
0,R6 R10 R17 R19 R20 R26 R27 R75 R76 R77 R78 R79,,CSR1206FT1R00,RC0402FR-0720KL,RC0402FR-0768K1L,RC0402JR-070RL,311-0.0JRCT-ND,311-20.0KLRCT-ND,CSR1206FT1R00CT-ND,YAG3213CT-ND
GT-TC029B-H025-L1N,SW1 SW2,,CS1213AGF260,2449-CS1213AGF260CT-ND,,,,,,
TPS546D24ARVFR,U2,,TPS546D24ARVFR,296-TPS546D24ARVFRCT-ND,,,,,,
RT9080-33GJ5,U3,,RT9080-33GJ5,1028-1509-1-ND,,,,,,
ESP32-S3-WROOM-1,U4,,ESP32-S3-WROOM-1-N16R8,1965-ESP32-S3-WROOM-1-N16R8CT-ND,,,,,,
SPX3819M5-L-1-8,U5,,,,,,,,,
24MHz,U7,,SX3M25.000E20F30THN,,C5137262,,,,,
~,U8,,,,,DNP,,,,
SN74AVC4T774,U9,,SN74AVC4T774PWR,296-24739-1-ND,,,,,,
EMC2101,U10,,EMC2101-R-ACZL-TR,EMC2101-R-ACZL-CT-ND,,,,,,
LM358,U23,,LM358LVIPWR,,,,,,,

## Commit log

2025-06-05 First Draft
    First draft of Bitshoka Nini
    A Bitaxe Gamma based miner with Whatsminer KF1950 ASIC
    Schematic needs some of the comms lines connected
    Layout needs placement and routing of the new Rs n Cs that came with the KF1950
2025-06-12 All components placed
    Went through TI schematic and layout checklist.
    All components placed and initial DRC
    Need thermal vias on KF1950 and also better layout (so not so many errors)
    Need to do silk
2025-06-13 Silk Done
    Still need to fix up heatsink vias on ASIC and paste layer for thermal
2025-06-17 PCB fixes
    Fixed up KF1950 footprint
    Added heatsinking to the bottom
2025-06-20 Manfacturing prep
    Add part numbers and did initial BOM optimization (Hope to do more after testing)
    Created Manufacturing files
2025-07-04 Addressed Bitaxe Gamma Issues
    - moved Fan caps
    - added USB CC1 & CC2 pulldowns
    - (I2C pullups were already done)
    - reviewed but so far did not address any of the other issues/bugs
2025-07-04 Forgot to update Manufacturing Outputs / Gerbers
    - Added Gerbers
    - Add PDF of schematic
2025-07-16 New Inductor & BOM fix
    Changed the inductor and cleaned up files for JLCPCB order.
2025-07-16 Fixed CMOS clock
2026-05-06 Add Bitshoka Pic
2026-05-06 Revise Bitshoka and Bitaxe project descriptions
    Initial update - still have lots to do.
